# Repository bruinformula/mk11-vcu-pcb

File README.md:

### Wow!!!
## Welcome!!
# Bruin Formula Racing
Mk. 11 VCU!

oh omid..... where do i even begin..... your leadership..... its everything i could ask for in an LV lead and more... the way you effortlessly lead LVSW meetings with such effortlessness and nonchalance is to be admired... you're a hero.. not just to me.. but to all of BFR LV... hope youre doing well...

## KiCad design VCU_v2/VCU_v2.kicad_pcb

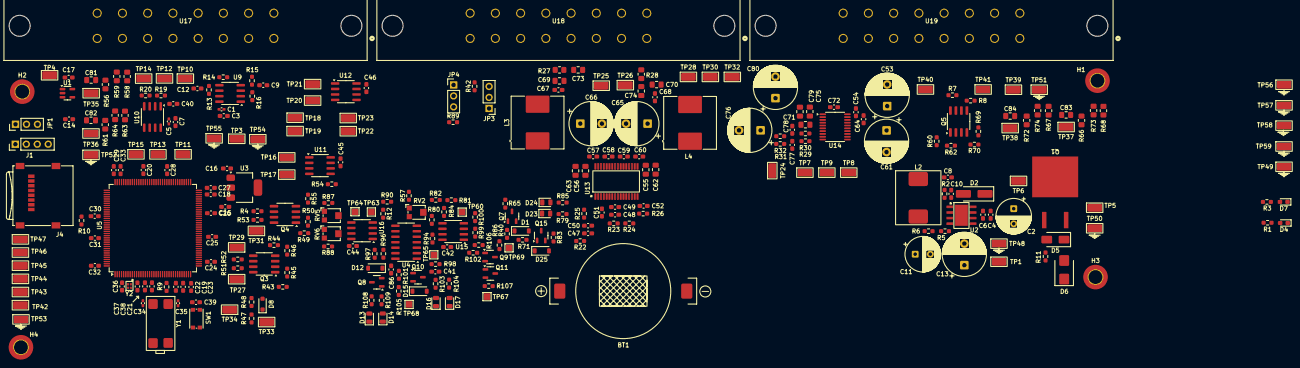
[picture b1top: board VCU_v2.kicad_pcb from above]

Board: 6 copper layers, 300 parts (0 on the bottom side), 159 nets, no tracks yet.

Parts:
BT1: 3.3V CR2032; Untitled
C1, C5: 22n; C_0402_1005Metric_Pad0.74x0.62mm_HandSolder
C2, C11: 100u; CP_Radial_D8.0mm_P3.50mm
C3, C7, C19, C20, C21, C22, C23, C24, C25, C26, C27, C28, C29, C30, C31, C32, C39, C45, C46, C47, C54, C64: 100n; C_0603_1608Metric_Pad1.08x0.95mm_HandSolder
C4, C6, C15, C16, C48, C51: 10u; C_0603_1608Metric_Pad1.08x0.95mm_HandSolder
C8, C50: 10n; C_0603_1608Metric_Pad1.08x0.95mm_HandSolder
C9, C12, C40: 47n; C_0603_1608Metric_Pad1.08x0.95mm_HandSolder
C10: 220p; C_0603_1608Metric_Pad1.08x0.95mm_HandSolder
C13, C65, C66: 220u; CP_Radial_D10.0mm_P5.00mm
C14, C17, C38, C49, C67, C68: 1u; C_0603_1608Metric_Pad1.08x0.95mm_HandSolder
C18, C33: 2.2p; C_0603_1608Metric_Pad1.08x0.95mm_HandSolder
C34, C35: 22p; C_0402_1005Metric_Pad0.74x0.62mm_HandSolder
C36, C37: 3.9p; C_0603_1608Metric_Pad1.08x0.95mm_HandSolder
C41, C42, C44, C86: 100nF; C_0603_1608Metric_Pad1.08x0.95mm_HandSolder
C52: 1.0n; C_0603_1608Metric_Pad1.08x0.95mm_HandSolder
C53, C61, C76, C80: 10u; CP_Radial_D10.0mm_P5.00mm
C55, C56, C69, C70: 1.0n; C_0805_2012Metric_Pad1.18x1.45mm_HandSolder
C57, C58, C59, C60: 220n; C_0603_1608Metric_Pad1.08x0.95mm_HandSolder
C62, C63, C75, C79, C81, C82, C83, C84: 100n; C_0805_2012Metric_Pad1.18x1.45mm_HandSolder
C71: 2.2u; C_0805_2012Metric_Pad1.18x1.45mm_HandSolder
C72: 2.2u; C_0603_1608Metric_Pad1.08x0.95mm_HandSolder
C73, C74: 10n; C_0805_2012Metric_Pad1.18x1.45mm_HandSolder
C77, C78: 2.2n; C_0603_1608Metric_Pad1.08x0.95mm_HandSolder
D1, D12, D15, D25: BZT52C16; D_SOD-123
D2: B340LA-13-F; D_SMA_Handsoldering
D4: GREEN LED; LED_0603_1608Metric_Pad1.05x0.95mm_HandSolder
D5: 27Vz; D_SMA
D6: SMBJ30CA; D_SMB
D7: BLUE LED; LED_0603_1608Metric_Pad1.05x0.95mm_HandSolder
D8: MM3Z3V3T1G; D_SOD-323_HandSoldering
D13, D14, D16, D17, D23, D24: Red; LED_0805_2012Metric
H1, H2, H3, H4: M3_Hole; MountingHole_3.2mm_M3_ISO7380_Pad_TopBottom
J1: Conn_01x04; PinHeader_1x04_P2.54mm_Vertical
J4: Micro_SD_Card; microSD_HC_Wuerth_693072010801
JP1, JP3, JP4: Jumper_3_Open; PinHeader_1x03_P2.54mm_Vertical
L2: 15u; Untitled
L3, L4: 10u; L_Coilcraft_MSS1260-XXX
Q1: PMOS; Untitled
Q3, Q4, Q5: SP8K80TB1; SOP-8_3.76x4.96mm_P1.27mm
Q7, Q15: SI2318CDS-T1-GE3; SOT-23-3
Q8, Q10: SI2347DS-T1-GE3; SOT-23-3
Q9, Q11: MMBT3904L RFG; SOT-23-3
R1, R31, R32, R48: 1.0k; R_0603_1608Metric_Pad0.98x0.95mm_HandSolder
R2: 56; R_0603_1608Metric_Pad0.98x0.95mm_HandSolder
R3, R4, R7, R8: 2.4k; R_0603_1608Metric_Pad0.98x0.95mm_HandSolder
R5, R10, R43, R44, R49, R51, R52, R53, R54, R60, R65, R69, R86, R94, R96, R97: 10k; R_0603_1608Metric_Pad0.98x0.95mm_HandSolder
R6: 3.3k; R_0603_1608Metric_Pad0.98x0.95mm_HandSolder
R9, R12, R80, R81, R82, R84: 0; R_0603_1608Metric_Pad0.98x0.95mm_HandSolder
R11, R25, R26, R57, R71, R87, R88, R90, R101, R105, R106, R107: 100k; R_0603_1608Metric_Pad0.98x0.95mm_HandSolder
R13, R15, R16, R19: 22k; R_0603_1608Metric_Pad0.98x0.95mm_HandSolder
R14, R20, R24: 47k; R_0603_1608Metric_Pad0.98x0.95mm_HandSolder
R22: 3.3; R_0603_1608Metric_Pad0.98x0.95mm_HandSolder
R23: 75k; R_0603_1608Metric_Pad0.98x0.95mm_HandSolder
R27, R28: 3.3; R_0805_2012Metric_Pad1.20x1.40mm_HandSolder
R29, R30: 470; R_0603_1608Metric_Pad0.98x0.95mm_HandSolder
R40, R45, R46, R50, R55, R62, R70: 100; R_0603_1608Metric_Pad0.98x0.95mm_HandSolder
R42, R89: 120; R_0603_1608Metric_Pad0.98x0.95mm_HandSolder
R47: 6.2k; R_0603_1608Metric_Pad0.98x0.95mm_HandSolder
R56, R61, R66, R72: 10k; R_0805_2012Metric_Pad1.20x1.40mm_HandSolder
R58, R59, R63, R64, R67, R68, R73, R74: 0; R_0805_2012Metric_Pad1.20x1.40mm_HandSolder
R79, R85, R103, R104, R108, R109: 510; R_0603_1608Metric_Pad0.98x0.95mm_HandSolder
R83: 51; R_0603_1608Metric_Pad0.98x0.95mm_HandSolder
R98: 3M; R_0603_1608Metric_Pad0.98x0.95mm_HandSolder
R99: 30k; R_0603_1608Metric_Pad0.98x0.95mm_HandSolder
R100: 120k; R_0603_1608Metric_Pad0.98x0.95mm_HandSolder
R102: 3k; R_0603_1608Metric_Pad0.98x0.95mm_HandSolder
RV2, RV5, RV6: 100k; Potentiometer_Bourns_TC33X_Vertical
SW1: SW_Push; SW_Push_1P1T_NO_CK_KMR2
TP1, TP3, TP4, TP5, TP6, TP7, TP8, TP9, TP10, TP11, TP12, TP13, TP14, TP15, TP16, TP17, TP18, TP19, TP20, TP21, TP22, TP23, TP24, TP25, TP26, TP27, TP28, TP29, TP30, TP31, TP32, TP33, TP34, TP35, TP36, TP37, TP38, TP39, TP40, TP41, TP42, TP43, TP44, TP45, TP46, TP47, TP48, TP49, TP50, TP51, TP52, TP53, TP54, TP55, TP56, TP57, TP58, TP59: RH-5015; TestPoint_Keystone_5015_Micro_Mini
TP60, TP63, TP64, TP65, TP67, TP68, TP69: TestPoint_Pad_1.5x1.5mm
U1: XC6221B481MR-G; SOT-23-5
U2: TPS5430; Untitled
U3: AMS1117-3.3; SOT-223-3_TabPin2
U4: CD4002BM96; SOIC-14_3.9x8.7mm_P1.27mm
U5: STM32H723ZGT6; LQFP-144_20x20mm_P0.5mm
U9, U10: TSB712AIDT; SOIC-8_3.9x4.9mm_P1.27mm
U11, U12: MCP2562FD-E/SN; SOIC-8_3.9x4.9mm_P1.27mm
U13: TPA3116D2QDADRQ1; Untitled
U14: PCM5102APWR; TSSOP-20_4.4x6.5mm_P0.65mm
U15, U16: LM393BIDR; SOIC-8_3.9x4.9mm_P1.27mm
U17, U18, U19: CONN_SD-19427-025_MOL
Y1: 16 MHz; Untitled
Y2: 32.768 kHz; Untitled

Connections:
12V: C42.2, C44.2, C86.2, D12.1 (K), D15.1 (K), Q8.2 (S), Q10.2 (S), R57.2, R81.2, R87.2, R94.2, R96.2, R97.2, R99.2, R102.2, RV6.1, U4.14 (VDD), U15.8 (VCC), U16.8 (VCC)
+3.3V: C16.1, C19.2, C20.2, C21.2, C22.2, C23.2, C24.2, C25.2, C26.2, C27.2, C28.2, C29.2, C30.2, C31.2, C32.2, C38.1, C45.1, C46.1, C53.1, C54.1, C75.1, C76.1, C79.1, C80.1, C81.1, C82.1, C83.1, C84.1, J1.1, J4.4 (VDD), JP1.1 (A), R51.2, R52.2, R53.2, R58.1, R63.1, R67.1, R73.1, TP3.1, U3.2 (VO), U5.17 (VDD), U5.30 (VDD), U5.32 (VREF+), U5.33 (VDDA), U5.39 (VDD), U5.52 (VDD), U5.62 (VDD), U5.72 (VDD), U5.84 (VDD), U5.95 (VDD33USB), U5.108 (VDD), U5.121 (VDD), U5.131 (VDD), U5.143 (PDR_ON), U5.144 (VDD), U11.5 (VIO), U12.5 (VIO), U14.1 (CPVDD), U14.8 (AVDD), U14.17 (XMT), U14.20 (DVDD)
+4.8V: C17.1, TP4.1, U1.5 (VOUT), U17.4, U17.5, U17.6
+5V: C1.1, C3.1, C5.1, C7.1, C11.1, C13.1, C14.1, C15.1, L2.2, R1.2, R5.2, TP1.1, U1.1 (VIN), U1.3 (CE), U3.3 (VI), U9.8 (VCC+), U10.8 (VCC+), U11.3 (VDD), U12.3 (VDD)
+12V: C2.1, C4.1, C6.1, C50.1, C55.1, C56.1, C62.1, C63.1, C65.1, C66.1, D5.1 (K), D6.2 (A2), Q1.3 (S), R3.2, R4.2, R7.2, R8.1, R22.2, R25.2, R65.1, R79.2, R85.2, R86.2, TP5.1, U2.7 (VIN), U13.17 (PVCC), U13.18 (PVCC), U13.19 (PVCC), U13.31 (PVCC), U13.32 (PVCC)
/BSE-SIG: R12.1, R19.2, R90.2, TP14.1, U15.6 (-), U17.3
/BSPD-FAULT: Q7.3 (D), R43.2, R45.1, R54.2, R55.1, R65.2, TP28.1, U18.4
/BSPD-Logic/BSPD-inv: Q9.3 (C), R40.1, R71.1, R86.1, TP69.1
/BSPD-Logic/Isense-active: U4.4, U4.5, U18.3
/BSPD-Logic/Isense-thresh: U4.9, U4.10, U18.2
/Connector-Root/APPS1-SIG: R15.2, TP10.1, U17.1
/Connector-Root/APPS2-SIG: R13.2, TP12.1, U17.2
/Connector-Root/BMS-FAULT: R44.2, R46.1, R60.2, R62.1, TP30.1, U18.6
/Connector-Root/BMS_FAULT+: Q5.7 (D), Q5.8 (D), R7.1, TP40.1, U19.8
/Connector-Root/BRAKE_LIGHT: R47.2, TP33.1, U19.5
/Connector-Root/BSPD_FAULT+: Q4.5 (D), Q4.6 (D), R4.1, TP39.1, U19.6
/Connector-Root/CAN1_H: R89.1, TP18.1, U11.7 (CAN_H), U17.13
/Connector-Root/CAN1_L: JP4.3 (B), TP19.1, U11.6 (CAN_L), U17.12
/Connector-Root/CAN2_H: R42.1, TP22.1, U12.7 (CAN_H), U18.11
/Connector-Root/CAN2_L: JP3.3 (B), TP23.1, U12.6 (CAN_L), U18.10
/Connector-Root/GEN_BTN1+: R73.2, U19.1
/Connector-Root/GEN_BTN1-: R68.2, U19.9
/Connector-Root/GEN_BTN2+: R67.2, U19.2
/Connector-Root/GEN_BTN2-: R74.2, U19.10
/Connector-Root/IMD-FAULT: R49.2, R50.1, R69.2, R70.1, TP32.1, U18.5
/Connector-Root/IMD_FAULT+: Q5.5 (D), Q5.6 (D), R8.2, TP41.1, U19.7
/Connector-Root/PRECHARGE_BTN+: R58.2, U17.15
/Connector-Root/PRECHARGE_BTN-: R59.2, U17.16
/Connector-Root/RTD_BTN+: R63.2, U17.8
/Connector-Root/RTD_BTN-: R64.2, U17.7
/Connector-Root/SPEAKER+: C67.1, C69.1, L3.2, R27.2, TP25.1, U18.8
/Connector-Root/SPEAKER-: C68.2, C70.2, L4.2, R28.1, TP26.1, U18.7
/Connector-Root/Vin+: Q1.1 (D), TP6.1, U18.1
/STM32-Root/RTD Audio/DAC_OUT: C51.1, R31.1, R32.2, TP24.1
/STM32-Root/STM32H723ZGT6/PA0: U5.34 (PA0), U19.13
/STM32-Root/STM32H723ZGT6/PA1: U5.35 (PA1), U19.12
/STM32-Root/STM32H723ZGT6/PA2: U5.36 (PA2), U19.11
/STM32-Root/STM32H723ZGT6/PA13: J1.4, U5.105 (PA13)
/STM32-Root/STM32H723ZGT6/PA14: J1.2, U5.109 (PA14)
/STM32-Root/STM32H723ZGT6/PB5: TP20.1, U5.135 (PB5), U12.4 (RXD)
/STM32-Root/STM32H723ZGT6/PB6: TP21.1, U5.136 (PB6), U12.1 (TXD)
/STM32-Root/STM32H723ZGT6/PB10: TP7.1, U5.69 (PB10), U14.13 (BCK)
/STM32-Root/STM32H723ZGT6/PB12: TP8.1, U5.73 (PB12), U14.15 (LRCK)
/STM32-Root/STM32H723ZGT6/PB13: J4.7 (DAT0), TP46.1, U5.74 (PB13)
/STM32-Root/STM32H723ZGT6/PB15: U5.76 (PB15), U17.14
/STM32-Root/STM32H723ZGT6/PC1: TP9.1, U5.27 (PC1), U14.14 (DIN)
/STM32-Root/STM32H723ZGT6/PC2: TP11.1, U5.28 (PC2_C), U9.1, U9.2 (IN1-)
/STM32-Root/STM32H723ZGT6/PC9: J4.8 (DAT1), TP47.1, U5.99 (PC9)
/STM32-Root/STM32H723ZGT6/PC10: J4.1 (DAT2), TP42.1, U5.111 (PC10)
/STM32-Root/STM32H723ZGT6/PC11: J4.2 (DAT3/CD), TP43.1, U5.112 (PC11)
/STM32-Root/STM32H723ZGT6/PC12: J4.5 (CLK), TP45.1, U5.113 (PC12)
/STM32-Root/STM32H723ZGT6/PD0: TP17.1, U5.114 (PD0), U11.4 (RXD)
/STM32-Root/STM32H723ZGT6/PD1: TP16.1, U5.115 (PD1), U11.1 (TXD)
/STM32-Root/STM32H723ZGT6/PD2: J4.3 (CMD), TP44.1, U5.116 (PD2)
/STM32-Root/STM32H723ZGT6/PE7: Q3.5 (D), Q3.6 (D), R52.1, TP29.1, U5.58 (PE7)
/STM32-Root/STM32H723ZGT6/PE8: Q4.7 (D), Q4.8 (D), R53.1, TP31.1, U5.59 (PE8)
/STM32-Root/STM32H723ZGT6/PE9: Q3.7 (D), Q3.8 (D), R51.1, TP27.1, U5.60 (PE9)
/STM32-Root/STM32H723ZGT6/PE10: U5.63 (PE10), U18.15
/STM32-Root/STM32H723ZGT6/PE11: U5.64 (PE11), U18.16
/STM32-Root/STM32H723ZGT6/PF8: TP15.1, U5.20 (PF8), U10.1, U10.2 (IN1-)
/STM32-Root/STM32H723ZGT6/PF10: TP13.1, U5.22 (PF10), U9.6 (IN2-), U9.7
/STM32-Root/STM32H723ZGT6/PF13: D8.1 (K), R47.1, R48.1, TP34.1, U5.53 (PF13)
/STM32-Root/STM32H723ZGT6/PF14: C81.2, R56.2, R59.1, TP35.1, U5.54 (PF14)
/STM32-Root/STM32H723ZGT6/PF15: C82.2, R61.2, R64.1, TP36.1, U5.55 (PF15)
/STM32-Root/STM32H723ZGT6/PG0: C83.2, R66.2, R68.1, TP37.1, U5.56 (PG0)
/STM32-Root/STM32H723ZGT6/PG1: C84.2, R72.2, R74.1, TP38.1, U5.57 (PG1)
/STM32-Root/STM32H723ZGT6/PG2: U5.87 (PG2), U19.3
/STM32-Root/STM32H723ZGT6/PG3: U5.88 (PG3), U19.4
/STM32-Root/STM32H723ZGT6/PG6: U5.91 (PG6), U18.14
/STM32-Root/STM32H723ZGT6/PG7: U5.92 (PG7), U18.13
/STM32-Root/STM32H723ZGT6/PG8: U5.93 (PG8), U18.12
/STM32-Root/STM32H723ZGT6/VBAT: BT1.1 (+), U5.6 (VBAT)
GND: BT1.2 (-), C1.2, C2.2, C3.2, C4.2, C5.2, C6.2, C7.2, C9.2, C11.2, C12.2, C13.2, C14.2, C15.2, C16.2, C17.2, C18.2, C19.1, C20.1, C21.1, C22.1, C23.1, C24.1, C25.1, C26.1, C27.1, C28.1, C29.1, C30.1, C31.1, C32.1, C33.2, C34.2, C35.2, C36.1, C37.1, C38.2, C39.2, C40.2, C41.1, C42.1, C44.1, C45.2, C46.2, C47.1, C48.2, C49.2, C50.2, C52.2, C53.2, C54.2, C55.2, C56.2, C61.2, C62.2, C63.2, C64.2, C65.2, C66.2, C67.2, C68.1, C69.2, C70.1, C71.2, C73.2, C74.1, C75.2, C76.2, C77.1, C78.1, C79.2, C80.2, C86.1, D1.2 (A), D2.2 (A), D4.1 (K), D6.1 (A1), D7.1 (K), D8.2 (A), D13.1 (K), D14.1 (K), D16.1 (K), D17.1 (K), J1.3, J4.6 (VSS), J4.9 (SHIELD), JP1.3 (B), Q3.1 (S), Q3.3 (S), Q4.1 (S), Q4.3 (S), Q5.1 (S), Q5.3 (S), Q7.2 (S), Q11.2 (E), R2.2, R6.2, R10.2, R11.2, R14.1, R16.1, R20.1, R24.1, R26.1, R43.1, R44.1, R48.2, R49.1, R54.1, R56.1, R60.1, R61.1, R66.1, R69.1, R72.1, R82.1, R83.1, R88.1, R90.1, R100.1, RV2.3, RV5.3, SW1.2, TP48.1, TP49.1, TP50.1, TP51.1, TP52.1, TP53.1, TP54.1, TP55.1, TP56.1, TP57.1, TP58.1, TP59.1, U1.2 (GND), U2.6 (GND), U2.9 (DAP), U3.1 (GND), U4.7 (VSS), U5.16 (VSS), U5.31 (VSSA), U5.38 (VSS), U5.51 (VSS), U5.61 (VSS), U5.83 (VSS), U5.94 (VSS), U5.107 (VSS), U5.120 (VSS), U5.130 (VSS), U9.4 (VCC-), U10.4 (VCC-), U10.5 (IN2+), U11.2 (VSS), U11.8 (STDBY), U12.2 (VSS), U12.8 (STDBY), U13.1 (MODESEL), U13.9 (GND), U13.10 (LINP), U13.11 (LINN), U13.13 (AM2), U13.14 (AM1), U13.15 (AM0), U13.22 (GND), U13.25 (GND), U13.28 (GND), U14.3 (CPGND), U14.9 (AGND), U14.10 (DEMP), U14.11 (FLT), U14.12 (SCK), U14.16 (FMT), U14.19 (DGND), U15.4 (GND), U16.4 (GND), U17.9, U17.10, U17.11, U18.9, U19.14, U19.15, U19.16, Y1.2, Y1.3, Y2.2
unnamed: C10.2, R2.1
unnamed: C18.1, U5.71 (VCAP)
unnamed: C33.1, U5.106 (VCAP)
unnamed: C35.1, R9.1, Y1.4
unnamed: C47.2, R22.1
unnamed: C73.1, R27.1
unnamed: C74.2, R28.2
unnamed: C77.2, R29.2, R31.2
unnamed: C78.2, R30.2, R32.1
unnamed: D1.1 (K), Q7.1 (G), R40.2
unnamed: C8.1, C10.1, D2.1 (K), L2.1, U2.8 (PH)
unnamed: D4.2 (A), R1.1
unnamed: D5.2 (A), Q1.2 (G), R11.1
unnamed: D7.2 (A), R3.1
unnamed: D12.2 (A), Q8.1 (G), R105.2
unnamed: D13.2 (A), R108.1
unnamed: D14.2 (A), R109.1
unnamed: D15.2 (A), Q10.1 (G), R101.2
unnamed: D16.2 (A), R103.1
unnamed: D17.2 (A), R104.1
unnamed: D23.2 (A), R79.1
unnamed: D23.1 (K), D24.1 (K), Q15.3 (D)
unnamed: D24.2 (A), R85.1
unnamed: D25.2 (A), Q15.2 (S), R83.2
unnamed: D25.1 (K), Q15.1 (G), R71.2
unnamed: JP1.2 (C), R10.1, U5.138 (BOOT0)
unnamed: JP3.2 (C), R42.2
unnamed: JP4.2 (C), R89.2
unnamed: Q3.2 (G), R45.2
unnamed: Q3.4 (G), R46.2
unnamed: Q4.2 (G), R50.2
unnamed: Q4.4 (G), R55.2
unnamed: Q5.2 (G), R62.2
unnamed: Q5.4 (G), R70.2
unnamed: Q8.3 (D), R108.2, R109.2
unnamed: Q9.1 (B), R106.2
unnamed: Q10.3 (D), R103.2, R104.2
unnamed: Q11.1 (B), R107.2
unnamed: Q9.2 (E), Q11.3 (C)
unnamed: R57.1, RV2.1
unnamed: R80.1, RV2.2
unnamed: R81.1, R82.2, R84.1
unnamed: R87.1, RV5.1
unnamed: R88.2, RV6.3
unnamed: R94.1, TP65.1, U4.2, U4.3, U15.7
unnamed: R96.1, U4.11, U16.1
unnamed: R97.1, U4.12, U16.7
unnamed: R98.1, U4.1
unnamed: R101.1, R107.1, TP67.1, U4.13
unnamed: R102.1, R105.1, R106.1, TP68.1, U15.1
unnamed: C8.2, U2.1 (BOOT)
unnamed: R5.1, R6.1, U2.4 (VSENSE)
unnamed: C39.1, SW1.1, U5.25 (NRST)
unnamed: C36.2, U5.8 (PC14-OSC32_IN), Y2.3
unnamed: C37.2, U5.9 (PC15-OSC32_OUT), Y2.1
unnamed: C34.1, U5.23 (PH0-OSC_IN), Y1.1
unnamed: R9.2, U5.24 (PH1-OSC_OUT)
unnamed: C9.1, R15.1, R16.2, U9.3 (IN1+)
unnamed: C12.1, R13.1, R14.2, U9.5 (IN2+)
unnamed: C40.1, R19.1, R20.2, U10.3 (IN1+)
unnamed: U10.6 (IN2-), U10.7
unnamed: C60.1, U13.20 (BSNL)
unnamed: C58.1, U13.26 (BSNR)
unnamed: C59.1, U13.24 (BSPL)
unnamed: C57.1, U13.30 (BSPR)
unnamed: R23.1, R24.2, U13.8 (GAIN/SLV)
unnamed: C49.1, R23.2, U13.6 (PLIMIT), U13.7 (GVDD)
unnamed: R26.2, U13.12 (MUTE)
unnamed: C59.2, C60.2, L4.1, U13.21 (OUTNL), U13.23 (OUTPL)
unnamed: C57.2, C58.2, L3.1, U13.27 (OUTNR), U13.29 (OUTPR)
unnamed: C48.1, U13.5 (RINN)
unnamed: C51.2, U13.4 (RINP)
unnamed: R25.1, U13.2 (SD)
unnamed: C52.1, U13.16 (SYNC)
unnamed: C72.1, U14.4 (CAPM)
unnamed: C72.2, U14.2 (CAPP)
unnamed: C61.1, C64.1, U14.18 (LDOO)
unnamed: R30.1, U14.6 (OUTL)
unnamed: R29.1, U14.7 (OUTR)
unnamed: C71.1, U14.5 (VNEG)
unnamed: R99.1, R100.2, U15.3 (+)
unnamed: C41.2, R98.2, U15.2 (-)
unnamed: R80.2, R84.2, TP60.1, U15.5 (+)
unnamed: RV5.2, TP63.1, U16.3 (+)
unnamed: R12.2, U16.2 (-), U16.5 (+)
unnamed: RV6.2, TP64.1, U16.6 (-)

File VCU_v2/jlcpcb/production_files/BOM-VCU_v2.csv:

Comment,Designator,Footprint,LCSC,Quantity
0,"R58,R59,R63,R64,R67,R68,R73,R74",R_0805_2012Metric_Pad1.20x1.40mm_HandSolder,C17477,8
0,"R12,R81,R84",R_0603_1608Metric_Pad0.98x0.95mm_HandSolder,C21189,3
0,R9,R_0603_1608Metric_Pad0.98x0.95mm_HandSolder,C22859,1
1.0k,"R1,R31,R32,R48",R_0603_1608Metric_Pad0.98x0.95mm_HandSolder,C21190,4
1.0n,C52,C_0603_1608Metric_Pad1.08x0.95mm_HandSolder,C1588,1
1.0n,"C55,C56,C69,C70",C_0805_2012Metric_Pad1.18x1.45mm_HandSolder,C46653,4
100,"R17,R40,R45,R46,R50,R55,R62",R_0603_1608Metric_Pad0.98x0.95mm_HandSolder,C22775,7
100k,"R101,R105,R106,R107,R11,R25,R26,R57,R71,R87,R88,R90",R_0603_1608Metric_Pad0.98x0.95mm_HandSolder,C25803,12
100k,"RV2,RV5,RV6",Potentiometer_Bourns_TC33X_Vertical,C719186,3
100n,"C19,C20,C21,C22,C23,C24,C25,C26,C27,C28,C29,C3,C30,C31,C32,C39,C45,C46,C47,C54,C64,C7",C_0603_1608Metric_Pad1.08x0.95mm_HandSolder,C14663,22
100n,"C62,C63,C75,C79,C81,C82,C83,C84",C_0805_2012Metric_Pad1.18x1.45mm_HandSolder,C28233,8
100nF,"C41,C42,C44,C86",C_0603_1608Metric_Pad1.08x0.95mm_HandSolder,C14663,4
10k,"R56,R61,R66,R72",R_0805_2012Metric_Pad1.20x1.40mm_HandSolder,C17414,4
10k,"R10,R43,R44,R49,R5,R51,R52,R53,R54,R60,R65,R8,R86,R94,R96,R97",R_0603_1608Metric_Pad0.98x0.95mm_HandSolder,C25804,16
10n,"C73,C74",C_0805_2012Metric_Pad1.18x1.45mm_HandSolder,C1710,2
10n,"C50,C8",C_0603_1608Metric_Pad1.08x0.95mm_HandSolder,C57112,2
10u,"C15,C16,C4,C48,C51,C6",C_0603_1608Metric_Pad1.08x0.95mm_HandSolder,C19702,6
120,"R42,R89",R_0603_1608Metric_Pad0.98x0.95mm_HandSolder,C22787,2
120k,R100,R_0603_1608Metric_Pad0.98x0.95mm_HandSolder,C25808,1
1u,"C14,C17,C38,C49,C67,C68",C_0603_1608Metric_Pad1.08x0.95mm_HandSolder,C15849,6
2.2n,"C77,C78",C_0603_1608Metric_Pad1.08x0.95mm_HandSolder,C1604,2
2.2p,"C18,C33",C_0603_1608Metric_Pad1.08x0.95mm_HandSolder,C1651,2
2.2u,C72,C_0603_1608Metric_Pad1.08x0.95mm_HandSolder,C23630,1
2.2u,C71,C_0805_2012Metric_Pad1.18x1.45mm_HandSolder,C377773,1
2.4k,"R18,R3,R4,R7",R_0603_1608Metric_Pad0.98x0.95mm_HandSolder,C22940,4
220n,"C57,C58,C59,C60",C_0603_1608Metric_Pad1.08x0.95mm_HandSolder,C21120,4
220p,C10,C_0603_1608Metric_Pad1.08x0.95mm_HandSolder,C1603,1
22k,"R13,R15,R16,R19",R_0603_1608Metric_Pad0.98x0.95mm_HandSolder,C31850,4
22n,"C1,C5",C_0402_1005Metric_Pad0.74x0.62mm_HandSolder,C1532,2
22p,"C34,C35",C_0402_1005Metric_Pad0.74x0.62mm_HandSolder,C1555,2
27Vz,D5,D_SMA,C712317,1
3.3,"R27,R28",R_0805_2012Metric_Pad1.20x1.40mm_HandSolder,C16257,2
3.3,R22,R_0603_1608Metric_Pad0.98x0.95mm_HandSolder,C22979,1
3.3k,R6,R_0603_1608Metric_Pad0.98x0.95mm_HandSolder,C22978,1
3.9p,"C36,C37",C_0603_1608Metric_Pad1.08x0.95mm_HandSolder,C1662,2
30k,R99,R_0603_1608Metric_Pad0.98x0.95mm_HandSolder,C22984,1
32.768 kHz,Y2,Untitled,C435180,1
3M,R98,R_0603_1608Metric_Pad0.98x0.95mm_HandSolder,C23156,1
3k,R102,R_0603_1608Metric_Pad0.98x0.95mm_HandSolder,C4211,1
470,"R29,R30",R_0603_1608Metric_Pad0.98x0.95mm_HandSolder,C23179,2
47k,"R14,R20,R24",R_0603_1608Metric_Pad0.98x0.95mm_HandSolder,C25819,3
47n,"C12,C40,C9",C_0603_1608Metric_Pad1.08x0.95mm_HandSolder,C1622,3
51,R83,R_0603_1608Metric_Pad0.98x0.95mm_HandSolder,C23197,1
510,"R103,R104,R108,R109,R79,R85",R_0603_1608Metric_Pad0.98x0.95mm_HandSolder,C23193,6
56,R2,R_0603_1608Metric_Pad0.98x0.95mm_HandSolder,C25196,1
6.2k,R47,R_0603_1608Metric_Pad0.98x0.95mm_HandSolder,C4260,1
75k,R23,R_0603_1608Metric_Pad0.98x0.95mm_HandSolder,C23242,1
AMS1117-3.3,U3,SOT-223-3_TabPin2,C6186,1
B340LA-13-F,D2,D_SMA_Handsoldering,C17101,1
BLUE LED,D7,LED_0603_1608Metric_Pad1.05x0.95mm_HandSolder,C99290,1
BZT52C16,"D1,D12,D15,D25",D_SOD-123,C2105,4
CD4002BM96,U4,SOIC-14_3.9x8.7mm_P1.27mm,C555144,1
GREEN LED,D4,LED_0603_1608Metric_Pad1.05x0.95mm_HandSolder,C125093,1
LM393BIDR,"U15,U16",SOIC-8_3.9x4.9mm_P1.27mm,C2865059,2
MCP2562FD-E/SN,"U11,U12",SOIC-8_3.9x4.9mm_P1.27mm,C124016,2
MM3Z3V3T1G,D8,D_SOD-323_HandSoldering,C75073,1
MMBT3904L RFG,"Q11,Q9",SOT-23-3,C81464,2
PCM5102APWR,U14,TSSOP-20_4.4x6.5mm_P0.65mm,C107671,1
PMOS,Q1,Untitled,C108357,1
RH-5015,"TP1,TP10,TP11,TP12,TP13,TP14,TP15,TP16,TP17,TP18,TP19,TP20,TP21,TP22,TP23,TP24,TP25,TP26,TP27,TP28,TP29,TP3,TP30,TP31,TP32,TP33,TP34,TP35,TP36,TP37,TP38,TP39,TP4,TP42,TP43,TP44,TP45,TP46,TP47,TP48,TP49,TP5,TP50,TP51,TP52,TP53,TP54,TP55,TP56,TP57,TP58,TP59,TP6,TP7,TP8,TP9",TestPoint_Keystone_5015_Micro_Mini,C5199798,56
Red,"D13,D14,D16,D17,D23,D24",LED_0805_2012Metric,C84256,6
SI2318CDS-T1-GE3,"Q15,Q7",SOT-23-3,C14498,2
SI2347DS-T1-GE3,"Q10,Q8",SOT-23-3,C145002,2
SMBJ30CA,D6,D_SMB,C8837,1
SP8K80TB1,"Q2,Q3,Q4",SOP-8_3.76x4.96mm_P1.27mm,C17689842,3
STM32H723ZGT6,U5,LQFP-144_20x20mm_P0.5mm,C7089881,1
TPA3116D2QDADRQ1,U13,Untitled,C2872892,1
TPS5430,U2,Untitled,C9864,1
TSB712AIDT,"U10,U9",SOIC-8_3.9x4.9mm_P1.27mm,C2971690,2
3.3V CR2032,BT1,Untitled,,1
~,TP63,TestPoint_Pad_1.5x1.5mm,,1
~,TP67,TestPoint_Pad_1.5x1.5mm,,1
220u,C65,CP_Radial_D10.0mm_P5.00mm,,1
~,U19,CONN_SD-19427-025_MOL,,1
100u,C11,CP_Radial_D8.0mm_P3.50mm,,1
100u,C2,CP_Radial_D8.0mm_P3.50mm,,1
SW_Push,SW1,SW_Push_1P1T_NO_CK_KMR2,,1
10u,L3,L_Coilcraft_MSS1260-XXX,,1
430450601,J2,CONN_SD-43045-001_06_MOL,,1
220u,C66,CP_Radial_D10.0mm_P5.00mm,,1
Conn_01x04,J1,PinHeader_1x04_P2.54mm_Vertical,,1
16 MHz,Y1,Untitled,,1
10u,C53,CP_Radial_D10.0mm_P5.00mm,,1
15u,L2,Untitled,,1
~,U18,CONN_SD-19427-025_MOL,,1
Micro_SD_Card,J4,microSD_HC_Wuerth_693072010801,,1
10u,C76,CP_Radial_D10.0mm_P5.00mm,,1
~,TP64,TestPoint_Pad_1.5x1.5mm,,1
10u,C61,CP_Radial_D10.0mm_P5.00mm,,1
~,U17,CONN_SD-19427-025_MOL,,1
~,TP60,TestPoint_Pad_1.5x1.5mm,,1
220u,C13,CP_Radial_D10.0mm_P5.00mm,,1
~,TP68,TestPoint_Pad_1.5x1.5mm,,1
~,TP65,TestPoint_Pad_1.5x1.5mm,,1
~,TP69,TestPoint_Pad_1.5x1.5mm,,1
10u,C80,CP_Radial_D10.0mm_P5.00mm,,1
XC6221B481MR-G,U1,SOT-23-5,,1
10u,L4,L_Coilcraft_MSS1260-XXX,,1

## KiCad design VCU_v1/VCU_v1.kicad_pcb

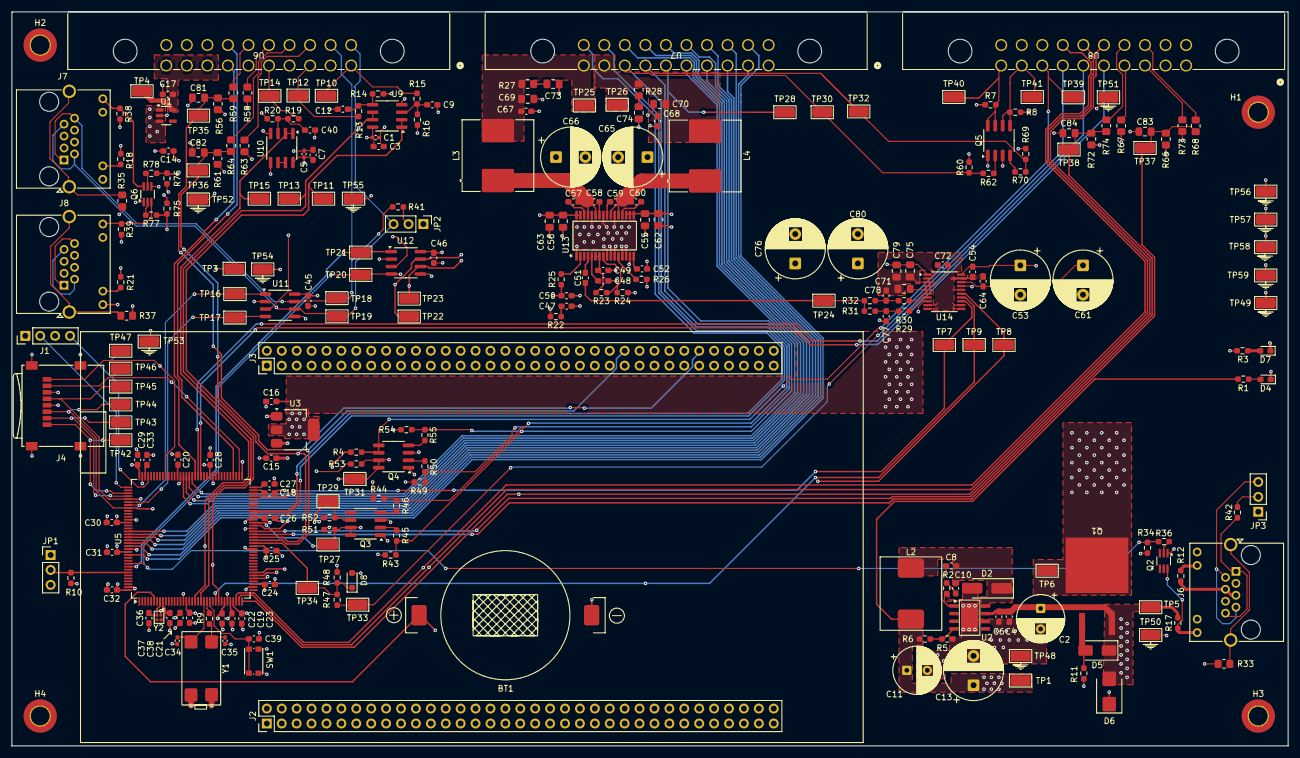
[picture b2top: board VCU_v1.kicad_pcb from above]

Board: 6 copper layers, 217.4 x 125.0 mm, 258 parts (0 on the bottom side), 146 nets.

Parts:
BT1: 3.3V CR2032; Untitled
C1, C5: 22n; C_0402_1005Metric_Pad0.74x0.62mm_HandSolder
C2, C11: 100u; CP_Radial_D8.0mm_P3.50mm
C3, C7, C19, C20, C21, C22, C23, C24, C25, C26, C27, C28, C29, C30, C31, C32, C39, C45, C46, C47, C54, C64: 100n; C_0603_1608Metric_Pad1.08x0.95mm_HandSolder
C4, C6, C15, C16, C48, C51: 10u; C_0603_1608Metric_Pad1.08x0.95mm_HandSolder
C8, C50: 10n; C_0603_1608Metric_Pad1.08x0.95mm_HandSolder
C9, C12, C40: 47n; C_0603_1608Metric_Pad1.08x0.95mm_HandSolder
C10: 220p; C_0603_1608Metric_Pad1.08x0.95mm_HandSolder
C13, C65, C66: 220u; CP_Radial_D10.0mm_P5.00mm
C14, C17, C38, C49, C67, C68: 1u; C_0603_1608Metric_Pad1.08x0.95mm_HandSolder
C18, C33: 2.2p; C_0603_1608Metric_Pad1.08x0.95mm_HandSolder
C34, C35: 22p; C_0402_1005Metric_Pad0.74x0.62mm_HandSolder
C36, C37: 3.9p; C_0603_1608Metric_Pad1.08x0.95mm_HandSolder
C52: 1.0n; C_0603_1608Metric_Pad1.08x0.95mm_HandSolder
C53, C61, C76, C80: 10u; CP_Radial_D10.0mm_P5.00mm
C55, C56, C69, C70: 1.0n; C_0805_2012Metric_Pad1.18x1.45mm_HandSolder
C57, C58, C59, C60: 220n; C_0603_1608Metric_Pad1.08x0.95mm_HandSolder
C62, C63, C75, C79, C81, C82, C83, C84: 100n; C_0805_2012Metric_Pad1.18x1.45mm_HandSolder
C71: 2.2u; C_0805_2012Metric_Pad1.18x1.45mm_HandSolder
C72: 2.2u; C_0603_1608Metric_Pad1.08x0.95mm_HandSolder
C73, C74: 10n; C_0805_2012Metric_Pad1.18x1.45mm_HandSolder
C77, C78: 2.2n; C_0603_1608Metric_Pad1.08x0.95mm_HandSolder
D2: B340LA-13-F; D_SMA_Handsoldering
D4: GREEN LED; LED_0603_1608Metric_Pad1.05x0.95mm_HandSolder
D5: 27Vz; D_SMA
D6: SMBJ30CA; D_SMB
D7: BLUE LED; LED_0603_1608Metric_Pad1.05x0.95mm_HandSolder
D8: MM3Z3V3T1G; D_SOD-323_HandSoldering
H1, H2, H3, H4: M3_Hole; MountingHole_3.2mm_M3_ISO7380_Pad_TopBottom
J1: Conn_01x04; PinHeader_1x04_P2.54mm_Vertical
J2: NUCLEO CONNECTOR LEFT; PinHeader_2x35_P2.54mm_Vertical
J3: NUCLEO CONNECTOR RIGHT; PinHeader_2x35_P2.54mm_Vertical
J4: Micro_SD_Card; microSD_HC_Wuerth_693072010801
J6, J7, J8: BRUHBus; RJ45_Amphenol_RJHSE538X
JP1, JP2, JP3: Jumper_3_Open; PinHeader_1x03_P2.54mm_Vertical
L2: 15u; Untitled
L3, L4: 10u; L_Coilcraft_MSS1260-XXX
Q1: PMOS; Untitled
Q2, Q6: BSD235NH6327XT; SOT-363_SC-70-6_Handsoldering
Q3, Q4, Q5: SP8K80TB1; SOP-8_3.76x4.96mm_P1.27mm
R1, R31, R32, R48: 1.0k; R_0603_1608Metric_Pad0.98x0.95mm_HandSolder
R2: 56; R_0603_1608Metric_Pad0.98x0.95mm_HandSolder
R3, R4, R7, R8, R12, R17, R18, R21, R38, R39: 2.4k; R_0603_1608Metric_Pad0.98x0.95mm_HandSolder
R5, R10, R34, R43, R44, R49, R51, R52, R53, R54, R60, R69, R75, R76: 10k; R_0603_1608Metric_Pad0.98x0.95mm_HandSolder
R6: 3.3k; R_0603_1608Metric_Pad0.98x0.95mm_HandSolder
R9: 0; R_0603_1608Metric_Pad0.98x0.95mm_HandSolder
R11, R25, R26: 100k; R_0603_1608Metric_Pad0.98x0.95mm_HandSolder
R13, R15, R16, R19: 22k; R_0603_1608Metric_Pad0.98x0.95mm_HandSolder
R14, R20, R24: 47k; R_0603_1608Metric_Pad0.98x0.95mm_HandSolder
R22: 3.3; R_0603_1608Metric_Pad0.98x0.95mm_HandSolder
R23: 75k; R_0603_1608Metric_Pad0.98x0.95mm_HandSolder
R27, R28: 3.3; R_0805_2012Metric_Pad1.20x1.40mm_HandSolder
R29, R30: 470; R_0603_1608Metric_Pad0.98x0.95mm_HandSolder
R33, R35, R37, R58, R59, R63, R64, R67, R68, R73, R74: 0; R_0805_2012Metric_Pad1.20x1.40mm_HandSolder
R36, R45, R46, R50, R55, R62, R70, R77, R78: 100; R_0603_1608Metric_Pad0.98x0.95mm_HandSolder
R41, R42: 120; R_0603_1608Metric_Pad0.98x0.95mm_HandSolder
R47: 6.2k; R_0603_1608Metric_Pad0.98x0.95mm_HandSolder
R56, R61, R66, R72: 10k; R_0805_2012Metric_Pad1.20x1.40mm_HandSolder
SW1: SW_Push; SW_Push_1P1T_NO_CK_KMR2
TP1, TP3, TP4, TP5, TP6, TP7, TP8, TP9, TP10, TP11, TP12, TP13, TP14, TP15, TP16, TP17, TP18, TP19, TP20, TP21, TP22, TP23, TP24, TP25, TP26, TP27, TP28, TP29, TP30, TP31, TP32, TP33, TP34, TP35, TP36, TP37, TP38, TP39, TP40, TP41, TP42, TP43, TP44, TP45, TP46, TP47, TP48, TP49, TP50, TP51, TP52, TP53, TP54, TP55, TP56, TP57, TP58, TP59: RH-5015; TestPoint_Keystone_5015_Micro_Mini
U1: XC6221B481MR-G; SOT-23-5
U2: TPS5430; Untitled
U3: AMS1117-3.3; SOT-223-3_TabPin2
U5: STM32H723ZGT6; LQFP-144_20x20mm_P0.5mm
U6, U7, U8: MX150 20-pin; CONN_SD-34829-001_20_ST_MOL
U9, U10: TSB712AIDT; SOIC-8_3.9x4.9mm_P1.27mm
U11, U12: MCP2562FD-E/SN; SOIC-8_3.9x4.9mm_P1.27mm
U13: TPA3116D2QDADRQ1; Untitled
U14: PCM5102APWR; TSSOP-20_4.4x6.5mm_P0.65mm
Y1: 16 MHz; Untitled
Y2: 32.768 kHz; Untitled

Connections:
+3.3V: C16.1, C19.2, C20.2, C21.2, C22.2, C23.2, C24.2, C25.2, C26.2, C27.2, C28.2, C29.2, C30.2, C31.2, C32.2, C38.1, C45.1, C46.1, C53.1, C54.1, C75.1, C76.1, C79.1, C80.1, C81.1, C82.1, C83.1, C84.1, J1.1, J4.4 (VDD), JP1.1 (A), R51.2, R52.2, R53.2, R58.1, R63.1, R67.1, R73.1, TP3.1, U3.2 (VO), U5.17 (VDD), U5.30 (VDD), U5.32 (VREF+), U5.33 (VDDA), U5.39 (VDD), U5.52 (VDD), U5.62 (VDD), U5.72 (VDD), U5.84 (VDD), U5.95 (VDD33USB), U5.108 (VDD), U5.121 (VDD), U5.131 (VDD), U5.143 (PDR_ON), U5.144 (VDD), U11.5 (VIO), U12.5 (VIO), U14.1 (CPVDD), U14.8 (AVDD), U14.17 (XMT), U14.20 (DVDD)
+4.8V: C17.1, TP4.1, U1.5 (VOUT), U6.8, U6.9, U6.10
+5V: C1.1, C3.1, C5.1, C7.1, C11.1, C13.1, C14.1, C15.1, J2.6, L2.2, R1.2, R5.2, TP1.1, U1.1 (VIN), U1.3 (CE), U3.3 (VI), U9.8 (VCC+), U10.8 (VCC+), U11.3 (VDD), U12.3 (VDD)
+12V: C2.1, C4.1, C6.1, C50.1, C55.1, C56.1, C62.1, C63.1, C65.1, C66.1, D5.1 (K), D6.2 (A2), J7.4 (+Vs), J7.5 (+Vs), J8.4 (+Vs), J8.5 (+Vs), Q1.3 (S), R3.2, R4.2, R7.2, R8.1, R17.2, R18.1, R21.1, R22.2, R25.2, R38.2, R39.2, TP5.1, U2.7 (VIN), U13.17 (PVCC), U13.18 (PVCC), U13.19 (PVCC), U13.31 (PVCC), U13.32 (PVCC)
/BRUHbus/CAN1_H: J7.1 (CANH_OUT), J7.8 (CANH_IN), R41.1, TP18.1, U6.12, U11.7 (CAN_H)
/BRUHbus/CAN1_L: J7.2 (CANL_OUT), J7.7 (CANL_IN), JP2.3 (B), TP19.1, U6.11, U11.6 (CAN_L)
/BRUHbus/CAN2_H: J6.1 (CANH_OUT), J6.8 (CANH_IN), J8.1 (CANH_OUT), J8.8 (CANH_IN), R42.1, TP22.1, U12.7 (CAN_H)
/BRUHbus/CAN2_L: J6.2 (CANL_OUT), J6.7 (CANL_IN), J8.2 (CANL_OUT), J8.7 (CANL_IN), JP3.3 (B), TP23.1, U12.6 (CAN_L)
/Connector-Root/APPS1-SIG: R15.2, TP10.1, U6.1
/Connector-Root/APPS2-SIG: R13.2, TP12.1, U6.3
/Connector-Root/BMS-FAULT: R44.2, R46.1, R60.2, R62.1, TP30.1, U7.8
/Connector-Root/BMS_FAULT+: Q5.7 (D), Q5.8 (D), R7.1, TP40.1, U8.10
/Connector-Root/BRAKE_LIGHT: R47.2, TP33.1, U8.7
/Connector-Root/BSE-SIG: R19.2, TP14.1, U6.5
/Connector-Root/BSPD-FAULT: R43.2, R45.1, R54.2, R55.1, TP28.1, U7.6
/Connector-Root/BSPD_FAULT+: Q4.5 (D), Q4.6 (D), R4.1, TP39.1, U8.8
/Connector-Root/GEN_BTN1+: R73.2, U8.3
/Connector-Root/GEN_BTN1-: R68.2, U8.13
/Connector-Root/GEN_BTN2+: R67.2, U8.4
/Connector-Root/GEN_BTN2-: R74.2, U8.14
/Connector-Root/IMD-FAULT: R49.2, R50.1, R69.2, R70.1, TP32.1, U7.7
/Connector-Root/IMD_FAULT+: Q5.5 (D), Q5.6 (D), R8.2, TP41.1, U8.9
/Connector-Root/PRECHARGE_BTN+: R58.2, U6.15
/Connector-Root/PRECHARGE_BTN-: R59.2, U6.16
/Connector-Root/RTD_BTN+: R63.2, U6.13
/Connector-Root/RTD_BTN-: R64.2, U6.14
/Connector-Root/SPEAKER+: C67.1, C69.1, L3.2, R27.2, TP25.1, U7.10
/Connector-Root/SPEAKER-: C68.2, C70.2, L4.2, R28.1, TP26.1, U7.9
/Connector-Root/Vin+: Q1.1 (D), TP6.1, U7.1
/STM32-Root/RTD Audio/DAC_OUT: C51.1, R31.1, R32.2, TP24.1
/STM32-Root/STM32H723ZGT6/PA0: J2.28, U5.34 (PA0), U8.17
/STM32-Root/STM32H723ZGT6/PA1: J2.30, U5.35 (PA1), U8.16
/STM32-Root/STM32H723ZGT6/PA2: J3.35, U5.36 (PA2), U8.15
/STM32-Root/STM32H723ZGT6/PA5: J3.11, U5.41 (PA5)
/STM32-Root/STM32H723ZGT6/PA6: J3.13, U5.42 (PA6)
/STM32-Root/STM32H723ZGT6/PA7: J3.15, U5.43 (PA7)
/STM32-Root/STM32H723ZGT6/PA13: J1.4, U5.105 (PA13)
/STM32-Root/STM32H723ZGT6/PA14: J1.2, U5.109 (PA14)
/STM32-Root/STM32H723ZGT6/PB5: J3.29, R34.2, R36.1, R76.2, R78.1, TP20.1, U5.135 (PB5), U12.4 (RXD)
/STM32-Root/STM32H723ZGT6/PB6: J3.17, TP21.1, U5.136 (PB6), U12.1 (TXD)
/STM32-Root/STM32H723ZGT6/PB10: J3.25, TP7.1, U5.69 (PB10), U14.13 (BCK)
/STM32-Root/STM32H723ZGT6/PB12: J3.16, TP8.1, U5.73 (PB12), U14.15 (LRCK)
/STM32-Root/STM32H723ZGT6/PB13: J3.30, J4.7 (DAT0), TP46.1, U5.74 (PB13)
/STM32-Root/STM32H723ZGT6/PB15: J3.26, U5.76 (PB15), U6.17
/STM32-Root/STM32H723ZGT6/PC1: J2.36, TP9.1, U5.27 (PC1), U14.14 (DIN)
/STM32-Root/STM32H723ZGT6/PC2: J2.35, TP11.1, U5.28 (PC2_C), U9.1, U9.2 (IN1-)
/STM32-Root/STM32H723ZGT6/PC9: J3.1, J4.8 (DAT1), TP47.1, U5.99 (PC9)
/STM32-Root/STM32H723ZGT6/PC10: J2.1, J4.1 (DAT2), TP42.1, U5.111 (PC10)
/STM32-Root/STM32H723ZGT6/PC11: J2.2, J4.2 (DAT3/CD), TP43.1, U5.112 (PC11)
/STM32-Root/STM32H723ZGT6/PC12: J2.3, J4.5 (CLK), TP45.1, U5.113 (PC12)
/STM32-Root/STM32H723ZGT6/PD0: J2.57, R75.2, R77.1, TP17.1, U5.114 (PD0), U11.4 (RXD)
/STM32-Root/STM32H723ZGT6/PD1: J2.55, TP16.1, U5.115 (PD1), U11.1 (TXD)
/STM32-Root/STM32H723ZGT6/PD2: J2.4, J4.3 (CMD), TP44.1, U5.116 (PD2)
/STM32-Root/STM32H723ZGT6/PE7: J3.44, Q3.5 (D), Q3.6 (D), R52.1, TP29.1, U5.58 (PE7)
/STM32-Root/STM32H723ZGT6/PE8: J3.40, Q4.7 (D), Q4.8 (D), R53.1, TP31.1, U5.59 (PE8)
/STM32-Root/STM32H723ZGT6/PE9: J3.52, Q3.7 (D), Q3.8 (D), R51.1, TP27.1, U5.60 (PE9)
/STM32-Root/STM32H723ZGT6/PE10: U5.63 (PE10), U7.19
/STM32-Root/STM32H723ZGT6/PE11: U5.64 (PE11), U7.20
/STM32-Root/STM32H723ZGT6/PF8: J2.54, TP15.1, U5.20 (PF8), U10.1, U10.2 (IN1-)
/STM32-Root/STM32H723ZGT6/PF10: J3.42, TP13.1, U5.22 (PF10), U9.6 (IN2-), U9.7
/STM32-Root/STM32H723ZGT6/PF13: D8.1 (K), R47.1, R48.1, TP34.1, U5.53 (PF13)
/STM32-Root/STM32H723ZGT6/PF14: C81.2, J3.50, R56.2, R59.1, TP35.1, U5.54 (PF14)
/STM32-Root/STM32H723ZGT6/PF15: C82.2, J3.60, R61.2, R64.1, TP36.1, U5.55 (PF15)
/STM32-Root/STM32H723ZGT6/PG0: C83.2, R66.2, R68.1, TP37.1, U5.56 (PG0)
/STM32-Root/STM32H723ZGT6/PG1: C84.2, R72.2, R74.1, TP38.1, U5.57 (PG1)
/STM32-Root/STM32H723ZGT6/PG2: U5.87 (PG2), U8.5
/STM32-Root/STM32H723ZGT6/PG3: U5.88 (PG3), U8.6
/STM32-Root/STM32H723ZGT6/PG4: U5.89 (PG4), U6.7
/STM32-Root/STM32H723ZGT6/PG5: U5.90 (PG5), U7.5
/STM32-Root/STM32H723ZGT6/PG6: U5.91 (PG6), U7.18
/STM32-Root/STM32H723ZGT6/PG7: U5.92 (PG7), U7.17
/STM32-Root/STM32H723ZGT6/PG8: U5.93 (PG8), U7.16
/STM32-Root/STM32H723ZGT6/PG9: U5.124 (PG9), U7.4
/STM32-Root/STM32H723ZGT6/PG10: U5.125 (PG10), U7.15
/STM32-Root/STM32H723ZGT6/PG11: U5.126 (PG11), U7.14
/STM32-Root/STM32H723ZGT6/PG12: U5.127 (PG12), U7.3
/STM32-Root/STM32H723ZGT6/PG13: U5.128 (PG13), U7.13
/STM32-Root/STM32H723ZGT6/PG14: U5.129 (PG14), U7.2
/STM32-Root/STM32H723ZGT6/PG15: U5.132 (PG15), U7.12
/STM32-Root/STM32H723ZGT6/VBAT: BT1.1 (+), J2.33, U5.6 (VBAT)
GND: BT1.2 (-), C1.2, C2.2, C3.2, C4.2, C5.2, C6.2, C7.2, C9.2, C11.2, C12.2, C13.2, C14.2, C15.2, C16.2, C17.2, C18.2, C19.1, C20.1, C21.1, C22.1, C23.1, C24.1, C25.1, C26.1, C27.1, C28.1, C29.1, C30.1, C31.1, C32.1, C33.2, C34.2, C35.2, C36.1, C37.1, C38.2, C39.2, C40.2, C45.2, C46.2, C47.1, C48.2, C49.2, C50.2, C52.2, C53.2, C54.2, C55.2, C56.2, C61.2, C62.2, C63.2, C64.2, C65.2, C66.2, C67.2, C68.1, C69.2, C70.1, C71.2, C73.2, C74.1, C75.2, C76.2, C77.1, C78.1, C79.2, C80.2, D2.2 (A), D4.1 (K), D6.1 (A1), D7.1 (K), D8.2 (A), J1.3, J2.8, J2.19, J2.20, J2.22, J2.49, J2.60, J3.9, J3.20, J3.32, J3.39, J3.54, J3.63, J4.6 (VSS), J4.9 (SHIELD), J6.9 (GND), J6.11 (GND), J7.3 (-Vs), J7.6 (-Vs), J7.9 (GND), J7.11 (GND), J8.3 (-Vs), J8.6 (-Vs), J8.9 (GND), J8.11 (GND), JP1.3 (B), Q2.1 (S), Q3.1 (S), Q3.3 (S), Q4.1 (S), Q4.3 (S), Q5.1 (S), Q5.3 (S), Q6.1 (S), Q6.4 (S), R2.2, R6.2, R10.2, R11.2, R14.1, R16.1, R20.1, R24.1, R26.1, R33.1, R34.1, R35.1, R37.1, R43.1, R44.1, R48.2, R49.1, R54.1, R56.1, R60.1, R61.1, R66.1, R69.1, R72.1, R75.1, R76.1, SW1.2, TP48.1, TP49.1, TP50.1, TP51.1, TP52.1, TP53.1, TP54.1, TP55.1, TP56.1, TP57.1, TP58.1, TP59.1, U1.2 (GND), U2.6 (GND), U2.9 (DAP), U3.1 (GND), U5.16 (VSS), U5.31 (VSSA), U5.38 (VSS), U5.51 (VSS), U5.61 (VSS), U5.83 (VSS), U5.94 (VSS), U5.107 (VSS), U5.120 (VSS), U5.130 (VSS), U6.18, U6.19, U6.20, U7.11, U8.18, U8.19, U8.20, U9.4 (VCC-), U10.4 (VCC-), U10.5 (IN2+), U11.2 (VSS), U11.8 (STDBY), U12.2 (VSS), U12.8 (STDBY), U13.1 (MODESEL), U13.9 (GND), U13.10 (LINP), U13.11 (LINN), U13.13 (AM2), U13.14 (AM1), U13.15 (AM0), U13.22 (GND), U13.25 (GND), U13.28 (GND), U14.3 (CPGND), U14.9 (AGND), U14.10 (DEMP), U14.11 (FLT), U14.12 (SCK), U14.16 (FMT), U14.19 (DGND), Y1.2, Y1.3, Y2.2
unnamed: C10.2, R2.1
unnamed: C18.1, U5.71 (VCAP)
unnamed: C33.1, U5.106 (VCAP)
unnamed: C35.1, R9.1, Y1.4
unnamed: C47.2, R22.1
unnamed: C73.1, R27.1
unnamed: C74.2, R28.2
unnamed: C77.2, R29.2, R31.2
unnamed: C78.2, R30.2, R32.1
unnamed: C8.1, C10.1, D2.1 (K), L2.1, U2.8 (PH)
unnamed: D4.2 (A), R1.1
unnamed: D5.2 (A), Q1.2 (G), R11.1
unnamed: D7.2 (A), R3.1
unnamed: J6.4 (+Vs), J6.5 (+Vs), R12.1
unnamed: J6.12 (CAN_IND), Q2.6 (D), R17.1
unnamed: J6.10 (POWER_GOOD), R12.2
unnamed: J6.SH (SHIELD), R33.2
unnamed: J7.12 (CAN_IND), Q6.6 (D), R38.1
unnamed: J7.10 (POWER_GOOD), R18.2
unnamed: J7.SH (SHIELD), R35.2
unnamed: J8.12 (CAN_IND), Q6.3 (D), R39.1
unnamed: J8.10 (POWER_GOOD), R21.2
unnamed: J8.SH (SHIELD), R37.2
unnamed: JP1.2 (C), R10.1, U5.138 (BOOT0)
unnamed: JP2.2 (C), R41.2
unnamed: JP3.2 (C), R42.2
unnamed: Q2.2 (G), R36.2
unnamed: Q3.2 (G), R45.2
unnamed: Q3.4 (G), R46.2
unnamed: Q4.2 (G), R50.2
unnamed: Q4.4 (G), R55.2
unnamed: Q5.2 (G), R62.2
unnamed: Q5.4 (G), R70.2
unnamed: Q6.2 (G), R77.2
unnamed: Q6.5 (G), R78.2
unnamed: C8.2, U2.1 (BOOT)
unnamed: R5.1, R6.1, U2.4 (VSENSE)
unnamed: C39.1, SW1.1, U5.25 (NRST)
unnamed: C36.2, U5.8 (PC14-OSC32_IN), Y2.3
unnamed: C37.2, U5.9 (PC15-OSC32_OUT), Y2.1
unnamed: C34.1, U5.23 (PH0-OSC_IN), Y1.1
unnamed: R9.2, U5.24 (PH1-OSC_OUT)
unnamed: C9.1, R15.1, R16.2, U9.3 (IN1+)
unnamed: C12.1, R13.1, R14.2, U9.5 (IN2+)
unnamed: C40.1, R19.1, R20.2, U10.3 (IN1+)
unnamed: U10.6 (IN2-), U10.7
unnamed: C60.1, U13.20 (BSNL)
unnamed: C58.1, U13.26 (BSNR)
unnamed: C59.1, U13.24 (BSPL)
unnamed: C57.1, U13.30 (BSPR)
unnamed: R23.1, R24.2, U13.8 (GAIN/SLV)
unnamed: C49.1, R23.2, U13.6 (PLIMIT), U13.7 (GVDD)
unnamed: R26.2, U13.12 (MUTE)
unnamed: C59.2, C60.2, L4.1, U13.21 (OUTNL), U13.23 (OUTPL)
unnamed: C57.2, C58.2, L3.1, U13.27 (OUTNR), U13.29 (OUTPR)
unnamed: C48.1, U13.5 (RINN)
unnamed: C51.2, U13.4 (RINP)
unnamed: R25.1, U13.2 (SD)
unnamed: C52.1, U13.16 (SYNC)
unnamed: C72.1, U14.4 (CAPM)
unnamed: C72.2, U14.2 (CAPP)
unnamed: C61.1, C64.1, U14.18 (LDOO)
unnamed: R30.1, U14.6 (OUTL)
unnamed: R29.1, U14.7 (OUTR)
unnamed: C71.1, U14.5 (VNEG)

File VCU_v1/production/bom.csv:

Designator,Footprint,Quantity,Value,LCSC Part #
BT1,Untitled,1,3.3V CR2032,
"C1, C5",0402,2,22n,C1532
C10,0603,1,220p,C1603
"C11, C2",CP_Radial_D8.0mm_P3.50mm,2,100u,
"C12, C40, C9",0603,3,47n,C1622
"C13, C65, C66",CP_Radial_D10.0mm_P5.00mm,3,220u,
"C14, C17, C38, C49, C67, C68",0603,6,1u,C15849
"C15, C16, C4, C48, C51, C6",0603,6,10u,C19702
"C18, C33",0603,2,2.2p,C1651
"C19, C20, C21, C22, C23, C24, C25, C26, C27, C28, C29, C3, C30, C31, C32, C39, C45, C46, C47, C54, C64, C7",0603,22,100n,C14663
"C34, C35",0402,2,22p,C1555
"C36, C37",0603,2,3.9p,C1662
"C50, C8",0603,2,10n,C57112
C52,0603,1,1.0n,C1588
"C53, C61, C76, C80",CP_Radial_D10.0mm_P5.00mm,4,10u,
"C55, C56, C69, C70",0805,4,1.0n,C46653
"C57, C58, C59, C60",0603,4,220n,C21120
"C62, C63, C75, C79, C81, C82, C83, C84",0805,8,100n,C28233
C71,0805,1,2.2u,C377773
C72,0603,1,2.2u,C23630
"C73, C74",0805,2,10n,C1710
"C77, C78",0603,2,2.2n,C1604
D2,D_SMA_Handsoldering,1,B340LA-13-F,C17101
D4,0603,1,GREEN LED,
D5,D_SMA,1,27Vz,C712317
D6,D_SMB,1,SMBJ30CA,C8837
D7,0603,1,BLUE LED,
D8,D_SOD-323_HandSoldering,1,MM3Z3V3T1G,C75073
J1,PinHeader_1x04_P2.54mm_Vertical,1,Conn_01x04,
J2,PinHeader_2x35_P2.54mm_Vertical,1,NUCLEO CONNECTOR LEFT,
J3,PinHeader_2x35_P2.54mm_Vertical,1,NUCLEO CONNECTOR RIGHT,
J4,microSD_HC_Wuerth_693072010801,1,Micro_SD_Card,
"J6, J7, J8",RJ45_Amphenol_RJHSE538X,3,BRUHBus,
L2,Untitled,1,15u,
"L3, L4",L_Coilcraft_MSS1260-XXX,2,10u,
Q1,Untitled,1,PMOS,C108357
"Q2, Q6",SOT-363_SC-70-6_Handsoldering,2,BSD235NH6327XT,
"Q3, Q4, Q5",SOP-8_3.76x4.96mm_P1.27mm,3,SP8K80TB1,C17689842
"R1, R31, R32, R48",0603,4,1.0k,C21190
"R10, R34, R43, R44, R49, R5, R51, R52, R53, R54, R60, R69, R75, R76",0603,14,10k,C25804
"R11, R25, R26",0603,3,100k,C25803
"R12, R17, R18, R21, R3, R38, R39, R4, R7, R8",0603,10,2.4k,C22940
"R13, R15, R16, R19",0603,4,22k,C31850
"R14, R20, R24",0603,3,47k,C25819
R2,0603,1,56,C25196
R22,0603,1,3.3,C22979
R23,0603,1,75k,C23242
"R27, R28",0805,2,3.3,C16257
"R29, R30",0603,2,470,C23179
"R33, R35, R37, R58, R59, R63, R64, R67, R68, R73, R74",0805,11,0,C17477
"R36, R45, R46, R50, R55, R62, R70, R77, R78",0603,9,100,C22775
"R41, R42",0603,2,120,C22787
R47,0603,1,6.2k,C4260
"R56, R61, R66, R72",0805,4,10k,C17414
R6,0603,1,3.3k,C22978
R9,0603,1,0,C22859
SW1,SW_Push_1P1T_NO_CK_KMR2,1,SW_Push,
"TP1, TP10, TP11, TP12, TP13, TP14, TP15, TP16, TP17, TP18, TP19, TP20, TP21, TP22, TP23, TP24, TP25, TP26, TP27, TP28, TP29, TP3, TP30, TP31, TP32, TP33, TP34, TP35, TP36, TP37, TP38, TP39, TP4, TP40, TP41, TP42, TP43, TP44, TP45, TP46, TP47, TP48, TP49, TP5, TP50, TP51, TP52, TP53, TP54, TP55, TP56, TP57, TP58, TP59, TP6, TP7, TP8, TP9",TestPoint_Keystone_5015_Micro_Mini,58,RH-5015,C5199798
U1,SOT-23-5,1,XC6221B481MR-G,
"U10, U9",SOIC-8_3.9x4.9mm_P1.27mm,2,TSB712AIDT,C2971690
"U11, U12",SOIC-8_3.9x4.9mm_P1.27mm,2,MCP2562FD-E/SN, C124016
U13,Untitled,1,TPA3116D2QDADRQ1,C2872892
U14,TSSOP-20_4.4x6.5mm_P0.65mm,1,PCM5102APWR,
U2,Untitled,1,TPS5430,C9864
U3,SOT-223-3_TabPin2,1,AMS1117-3.3,C6186
U5,LQFP-144_20x20mm_P0.5mm,1,STM32H723ZGT6,https://jlcpcb.com/partdetail/STMicroelectronics-STM32H723ZG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
"U6, U7, U8",CONN_SD-34829-001_20_ST_MOL,3,MX150 20-pin,
Y1,Untitled,1,16 MHz,
Y2,Untitled,1,32.768 kHz,C2595065
